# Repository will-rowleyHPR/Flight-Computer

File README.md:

# Garrus Flight Computer

Guidance And Roll Regulation Utility System (GARRUS)  

This flight computer will be designed and used for the Monash HPR 2024 Control Onboarding Project  
  
STATUS:   
  Schematic: First Draft Complete  
  PCB: Unfinished

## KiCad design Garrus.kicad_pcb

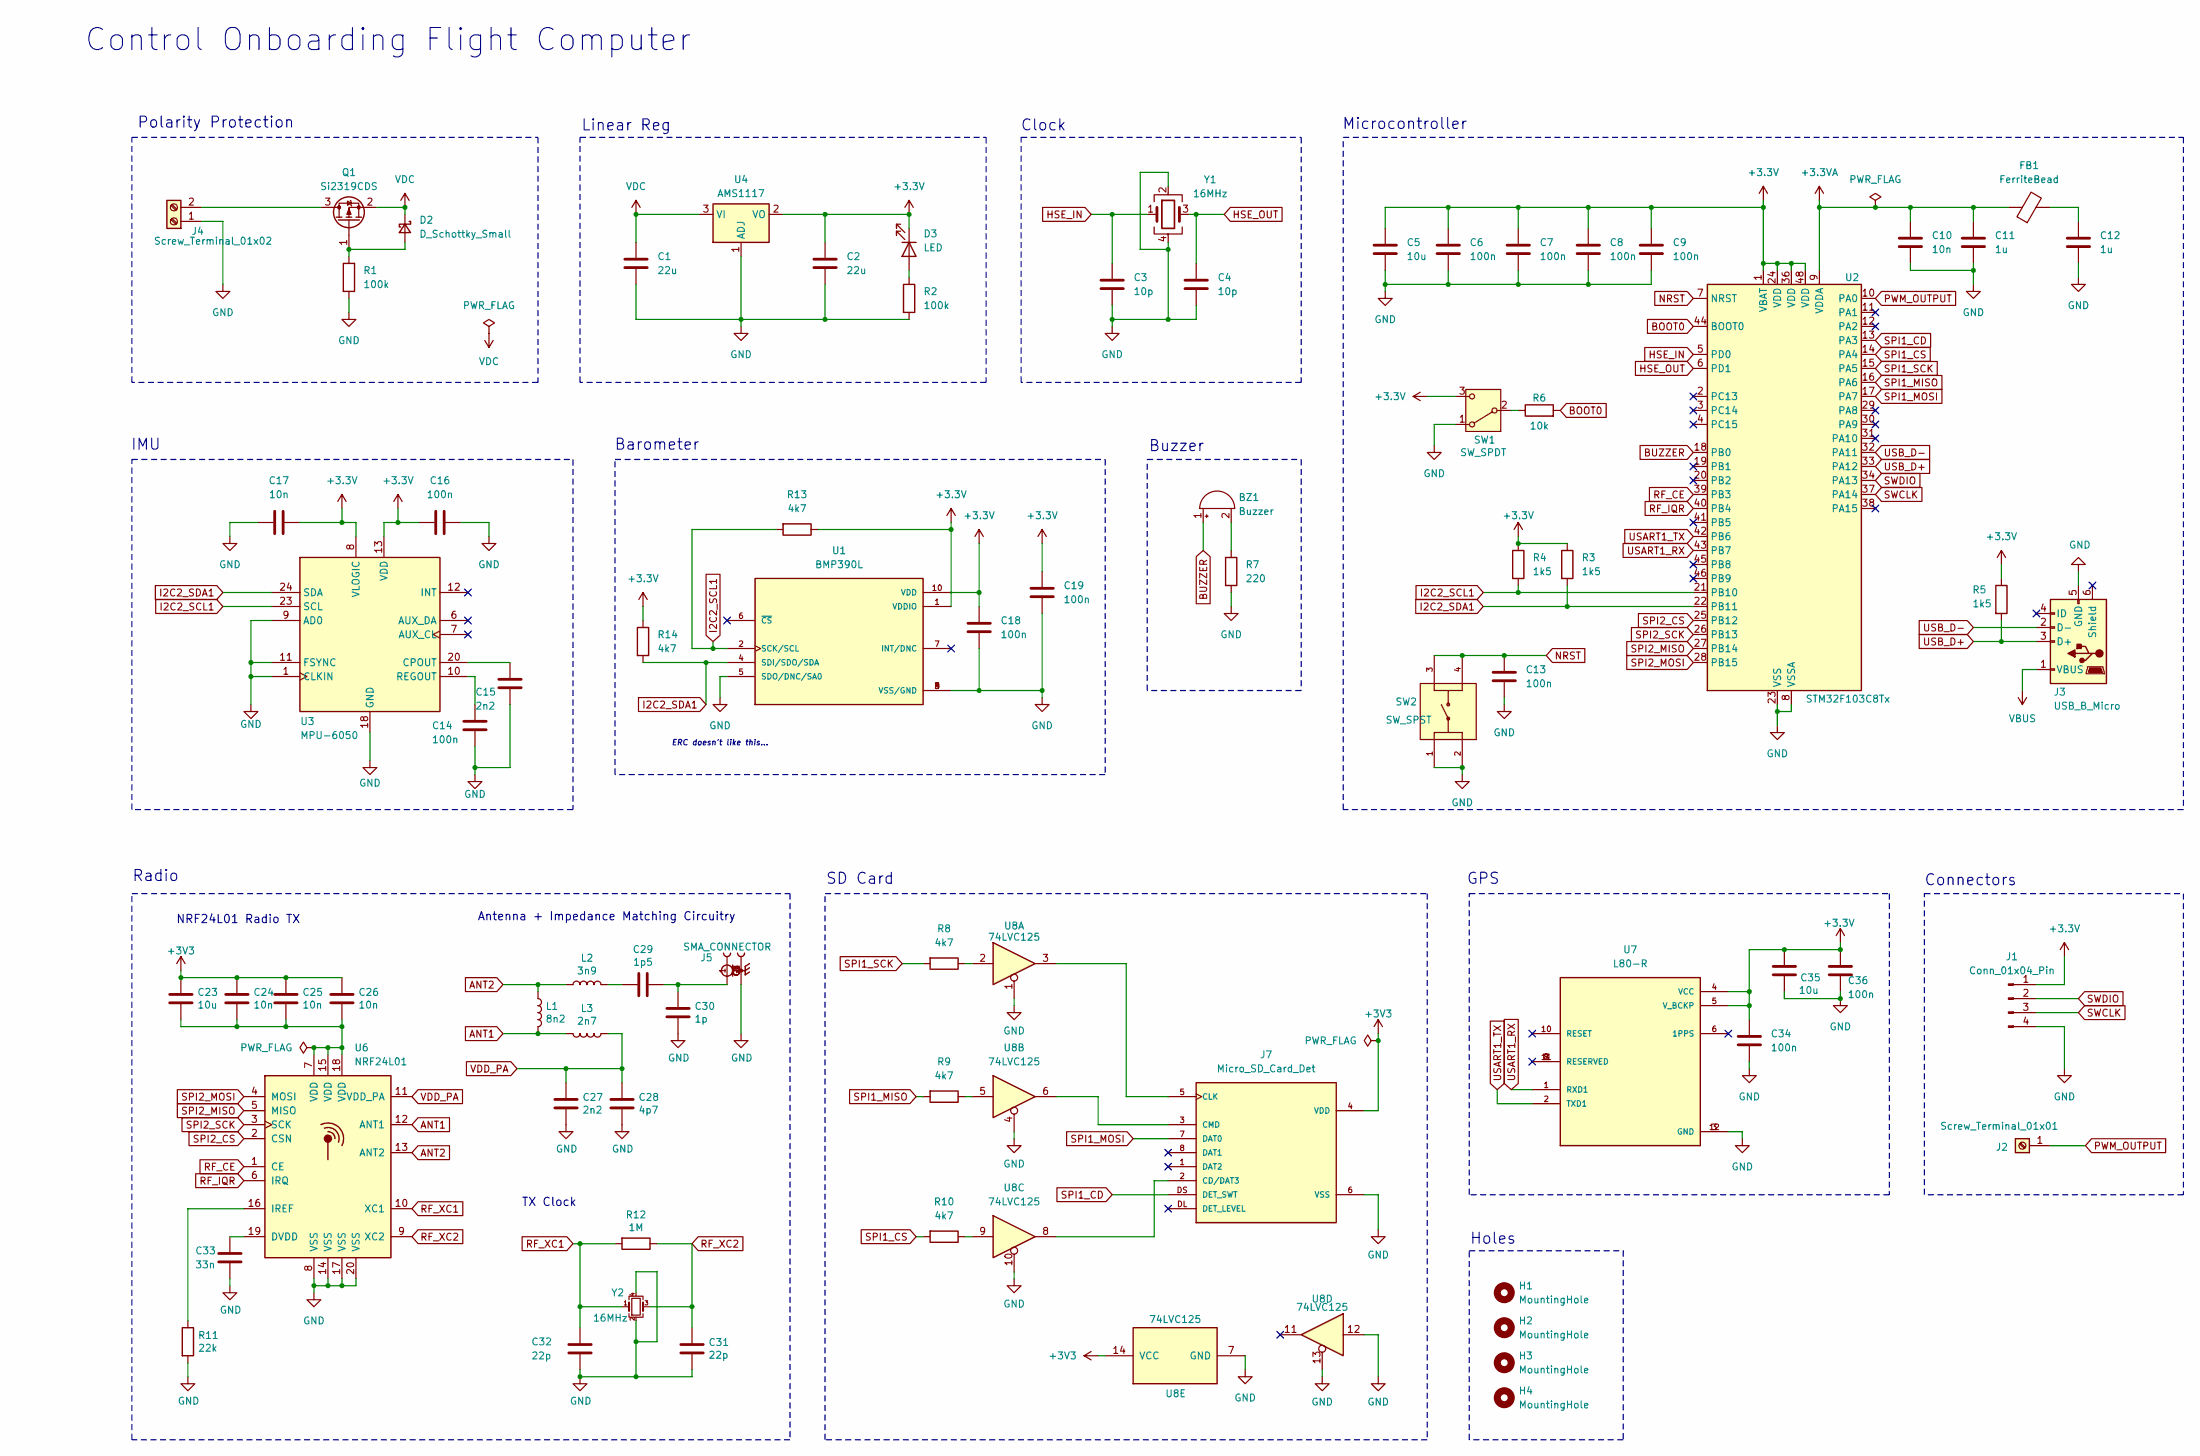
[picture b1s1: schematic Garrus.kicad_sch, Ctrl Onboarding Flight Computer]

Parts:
BZ1: Buzzer; Buzzer_12x9.5RM7.6
C1, C2: 22u; C_0805_2012Metric
C3, C4: 10p; C_0402_1005Metric
C5, C23, C35: 10u; C_0603_1608Metric
C6, C7, C8, C9, C13, C14, C16, C18, C19, C34, C36: 100n; C_0402_1005Metric
C10, C17, C24, C25, C26: 10n; C_0402_1005Metric
C11, C12: 1u; C_0402_1005Metric
C15, C27: 2n2; C_0402_1005Metric
C28: 4p7; C_0402_1005Metric
C29: 1p5; C_0402_1005Metric
C30: 1p; C_0402_1005Metric
C31, C32: 22p; C_0402_1005Metric
C33: 33n; C_0402_1005Metric
D2: D_Schottky_Small; D_SOD-523
D3: LED; LED_0603_1608Metric
FB1: FerriteBead; L_0603_1608Metric
H1, H2, H3, H4: MountingHole; MountingHole_2.2mm_M2
J1: Conn_01x04_Pin; JST_EH_B4B-EH-A_1x04_P2.50mm_Vertical
J2: Screw_Terminal_01x01; TerminalBlock_bornier-2_P5.08mm
J3: USB_B_Micro; USB_Micro-B_Wuerth_629105150521
J4: Screw_Terminal_01x02; TerminalBlock_bornier-2_P5.08mm
J5: SMA_CONNECTOR; LPRS_SMA_CONNECTOR; PARTREV 1.3
J7: Micro_SD_Card_Det; MOLEX_502570-0893
L1: 8n2; L_0402_1005Metric
L2: 3n9; L_0402_1005Metric
L3: 2n7; L_0402_1005Metric
Q1: Si2319CDS; SOT-23
R1, R2: 100k; R_0402_1005Metric
R3, R4, R5: 1k5; R_0402_1005Metric
R6: 10k; R_0402_1005Metric
R7: 220; R_0402_1005Metric
R8, R9, R10, R13, R14: 4k7; R_0402_1005Metric
R11: 22k; R_0402_1005Metric
R12: 1M; R_0402_1005Metric
SW1: SW_SPDT; SW_SPDT_PCM12
SW2: SW_SPST; SW_1825910-6-4; PARTREV C10
U1: BMP390L; XDCR_BMP390L; PARTREV 1.7
U2: STM32F103C8Tx; LQFP-48_7x7mm_P0.5mm
U3: MPU-6050; InvenSense_QFN-24_4x4mm_P0.5mm
U4: AMS1117; SOT-223-3_TabPin2
U6: NRF24L01; QFN-20-1EP_4x4mm_P0.5mm_EP2.5x2.5mm
U7: L80-R; XCVR_L80-R
U8: 74LVC125; IC_74LVC125APW_118
Y1, Y2: 16MHz; Crystal_SMD_3225-4Pin_3.2x2.5mm

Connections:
+3.3V: C2.1, C5.1, C6.1, C7.1, C8.1, C9.1, C16.1, C17.1, C18.1, C19.1, C34.1, C35.1, C36.1, D3.1 (K), J1.1, R3.1, R4.1, R5.1, R13.1, R14.1, SW1.3 (C), U1.1 (VDDIO), U1.10 (VDD), U2.1 (VBAT), U2.24 (VDD), U2.36 (VDD), U2.48 (VDD), U3.8 (VLOGIC), U3.13 (VDD), U4.2 (VO), U7.4 (VCC), U7.5 (V_BCKP)
+3.3VA: C10.1, C11.1, FB1.1, U2.9 (VDDA)
+3V3: C23.1, C24.1, C25.1, C26.1, J7.4 (VDD), U8.14 (VCC)
ANT1: L1.2, L3.2, U6.12 (ANT1)
ANT2: L1.1, L2.1, U6.13 (ANT2)
BOOT0: R6.2, U2.44 (BOOT0)
BUZZER: BZ1.1 (+), U2.18 (PB0)
GND: C1.2, C2.2, C3.2, C4.2, C5.2, C6.2, C7.2, C8.2, C9.2, C10.2, C11.2, C12.2, C13.2, C14.2, C15.2, C16.2, C17.2, C18.2, C19.2, C27.1, C28.1, C30.1, C31.2, C32.2, C33.2, C34.2, C35.2, C36.2, J1.4, J3.5 (GND), J4.1, J5.G1, J5.G2, J5.G3, J5.G4, J7.6 (VSS), R1.2, R2.2, R7.2, R11.2, SW1.1 (A), SW2.1, SW2.2, U1.3 (VSS/GND), U1.5 (SDO/DNC/SA0), U1.8 (VSS/GND), U1.9 (VSS/GND), U2.8 (VSSA), U2.23 (VSS), U2.35 (VSS), U2.47 (VSS), U3.1 (CLKIN), U3.9 (AD0), U3.11 (FSYNC), U3.18 (GND), U4.1 (ADJ), U6.8 (VSS), U6.14 (VSS), U6.17 (VSS), U6.20 (VSS), U7.3 (GND), U7.12 (GND), U8.1, U8.4, U8.7 (GND), U8.10, U8.12, U8.13, Y1.2, Y1.4, Y2.2, Y2.4
HSE_IN: C3.1, U2.5 (PD0), Y1.1
HSE_OUT: C4.1, U2.6 (PD1), Y1.3
I2C2_SCL1: R4.2, R13.2, U1.2 (SCK/SCL), U2.21 (PB10), U3.23 (SCL)
I2C2_SDA1: R3.2, R14.2, U1.4 (SDI/SDO/SDA), U2.22 (PB11), U3.24 (SDA)
NRST: C13.1, SW2.3, SW2.4, U2.7 (NRST)
unnamed: BZ1.2 (-), R7.1
unnamed: C12.1, FB1.2
unnamed: C23.2, C24.2, C25.2, C26.2, U6.7 (VDD), U6.15 (VDD), U6.18 (VDD)
unnamed: C29.1, C30.2, J5.1
unnamed: C29.2, L2.2
unnamed: D2.2 (A), Q1.1 (G), R1.1
unnamed: D3.2 (A), R2.1
unnamed: J4.2, Q1.3 (D)
unnamed: J7.2 (CD/DAT3), U8.8
unnamed: J7.5 (CLK), U8.3
unnamed: J7.3 (CMD), U8.6
unnamed: R8.1, U8.2
unnamed: R9.1, U8.5
unnamed: R10.1, U8.9
unnamed: R6.1, SW1.2 (B)
unnamed: C15.1, U3.20 (CPOUT)
unnamed: C14.1, U3.10 (REGOUT)
unnamed: C33.1, U6.19 (DVDD)
unnamed: R11.1, U6.16 (IREF)
PWM_OUTPUT: J2.1, U2.10 (PA0)
RF_CE: U2.39 (PB3), U6.1 (CE)
RF_IQR: U2.40 (PB4), U6.6 (IRQ)
RF_XC1: C32.1, R12.2, U6.10 (XC1), Y2.1
RF_XC2: C31.1, R12.1, U6.9 (XC2), Y2.3
SPI1_CD: J7.DS (DET_SWT), U2.13 (PA3)
SPI1_CS: R10.2, U2.14 (PA4)
SPI1_MISO: R9.2, U2.16 (PA6)
SPI1_MOSI: J7.7 (DAT0), U2.17 (PA7)
SPI1_SCK: R8.2, U2.15 (PA5)
SPI2_CS: U2.25 (PB12), U6.2 (CSN)
SPI2_MISO: U2.27 (PB14), U6.5 (MISO)
SPI2_MOSI: U2.28 (PB15), U6.4 (MOSI)
SPI2_SCK: U2.26 (PB13), U6.3 (SCK)
SWCLK: J1.3, U2.37 (PA14)
SWDIO: J1.2, U2.34 (PA13)
USART1_RX: U2.43 (PB7), U7.1 (RXD1)
USART1_TX: U2.42 (PB6), U7.2 (TXD1)
USB_D+: J3.3 (D+), R5.2, U2.33 (PA12)
USB_D-: J3.2 (D-), U2.32 (PA11)
VBUS: J3.1 (VBUS)
VDC: C1.1, D2.1 (K), Q1.2 (S), U4.3 (VI)
VDD_PA: C27.2, C28.2, L3.1, U6.11 (VDD_PA)

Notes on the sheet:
Antenna + Impedance Matching Circuitry
Buzzer
Holes
Barometer
SD Card
Microcontroller
Control Onboarding Flight Computer
Clock
NRF24L01 Radio TX
ERC doesn't like this...
Connectors
Radio
GPS
Linear Reg
TX Clock
Polarity Protection
IMU

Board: 2 copper layers, 76 parts (0 on the bottom side), 54 nets, no tracks yet.

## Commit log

2024-05-02 Delete
2024-05-06 Rename README.txt to README.md
